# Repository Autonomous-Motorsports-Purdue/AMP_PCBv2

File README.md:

# AMP PCB version 2

This PCB attempts to refine the v1 PCB to strip away extraneous components and achieve the best minimal set of components needed for drive, steering, and braking control

## Features

| Name                    | Current Status         | Notes |
|-------------------------|------------------------|-------|
| Foot switch             | Working                | Master enable for motor controller
| Forward throttle        | Working                | -
| Reverse throttle        | Working                | -
| Motor brake control     | Untested               | Primary braking system if working
| Emergency brake control | Working                | Mechanical brake actuator
| Steering                | Working                | 0-100% PWM duty cycle control
| LoRa remote control     | Partially tested       | -
| Watchdog timer          | Broken on Rev A        | -
| Hardware serial port    | Working                | -

---

## Technical Information
- [Teensy 4.0 front pinout](docs/img/Teensy_40_Front_Pinout.png)
- [Teensy 4.0 rear pinout](docs/img/Teensy_40_Rear_Pinout.png)
- [Emergency brake controller truth table](docs/img/Brake_Control_Signals.png)

### Useful links
- [RC Low-pass Filter Design for PWM](http://sim.okawa-denshi.jp/en/PWMtool.php)
- [Software setup for Teensy with Arduino](https://www.pjrc.com/teensy/tutorial.html)

---

## Part Numbers
| Part Number | Description |
|-------------|-------------|
| [776164-1](https://www.digikey.com/en/products/detail/te-connectivity-deutsch-ict-connectors/776164-1/2183727) | AMPSEAL (main motor controller connector) 35-pin connector
| [770520-1](https://www.digikey.com/en/products/detail/te-connectivity-amp-connectors/770520-1/744981) | AMPSEAL crimps

---

## Miscellaneous notes (to check)

- Create documentation for connectors (especially motor controller connector)
- Create complete BOM for PCB

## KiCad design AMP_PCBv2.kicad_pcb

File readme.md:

# AMP PCB version 2

This PCB attempts to refine the v1 PCB to strip away extraneous components and achieve the best minimal set of components needed for drive, steering, and braking control

## Minimal Feature Set

- 0-12 volt analog throttle signal
- digital drive mode control (12 volt logic level)
  - Foot switch (FS1)
  - Forward (FWD)
  - Reverse (REV)
- 12 volt frequency modulated PWM steering signal
  - //TODO: ADD THE FREQUENCY BOUNDS OF FULL LEFT AND FULL RIGHT
- digital brake control (5 volt logic level //FIXME: IS THIS CORRECT?, CHECK IF THIS IS LEVEL SHIFTED ON CURRENT BOARD)
  - 

## Extensions

- E-Brake
- Remote control

## Notes (to check)

- Throttle differential amplifier
  - Check if gain can be larger/smaller than 3.63 (for resistor selection)
  - Low pass filter for PWM->analog signal
- Motor controller
  - Add breakout pins when PCB ordered/tested
- FTDI breakout (check if needed for Teensy)
- Feather
  - Remote control pins
- Connectors
  - Test point connectors
  - Signal out connectors (talk to electrical)

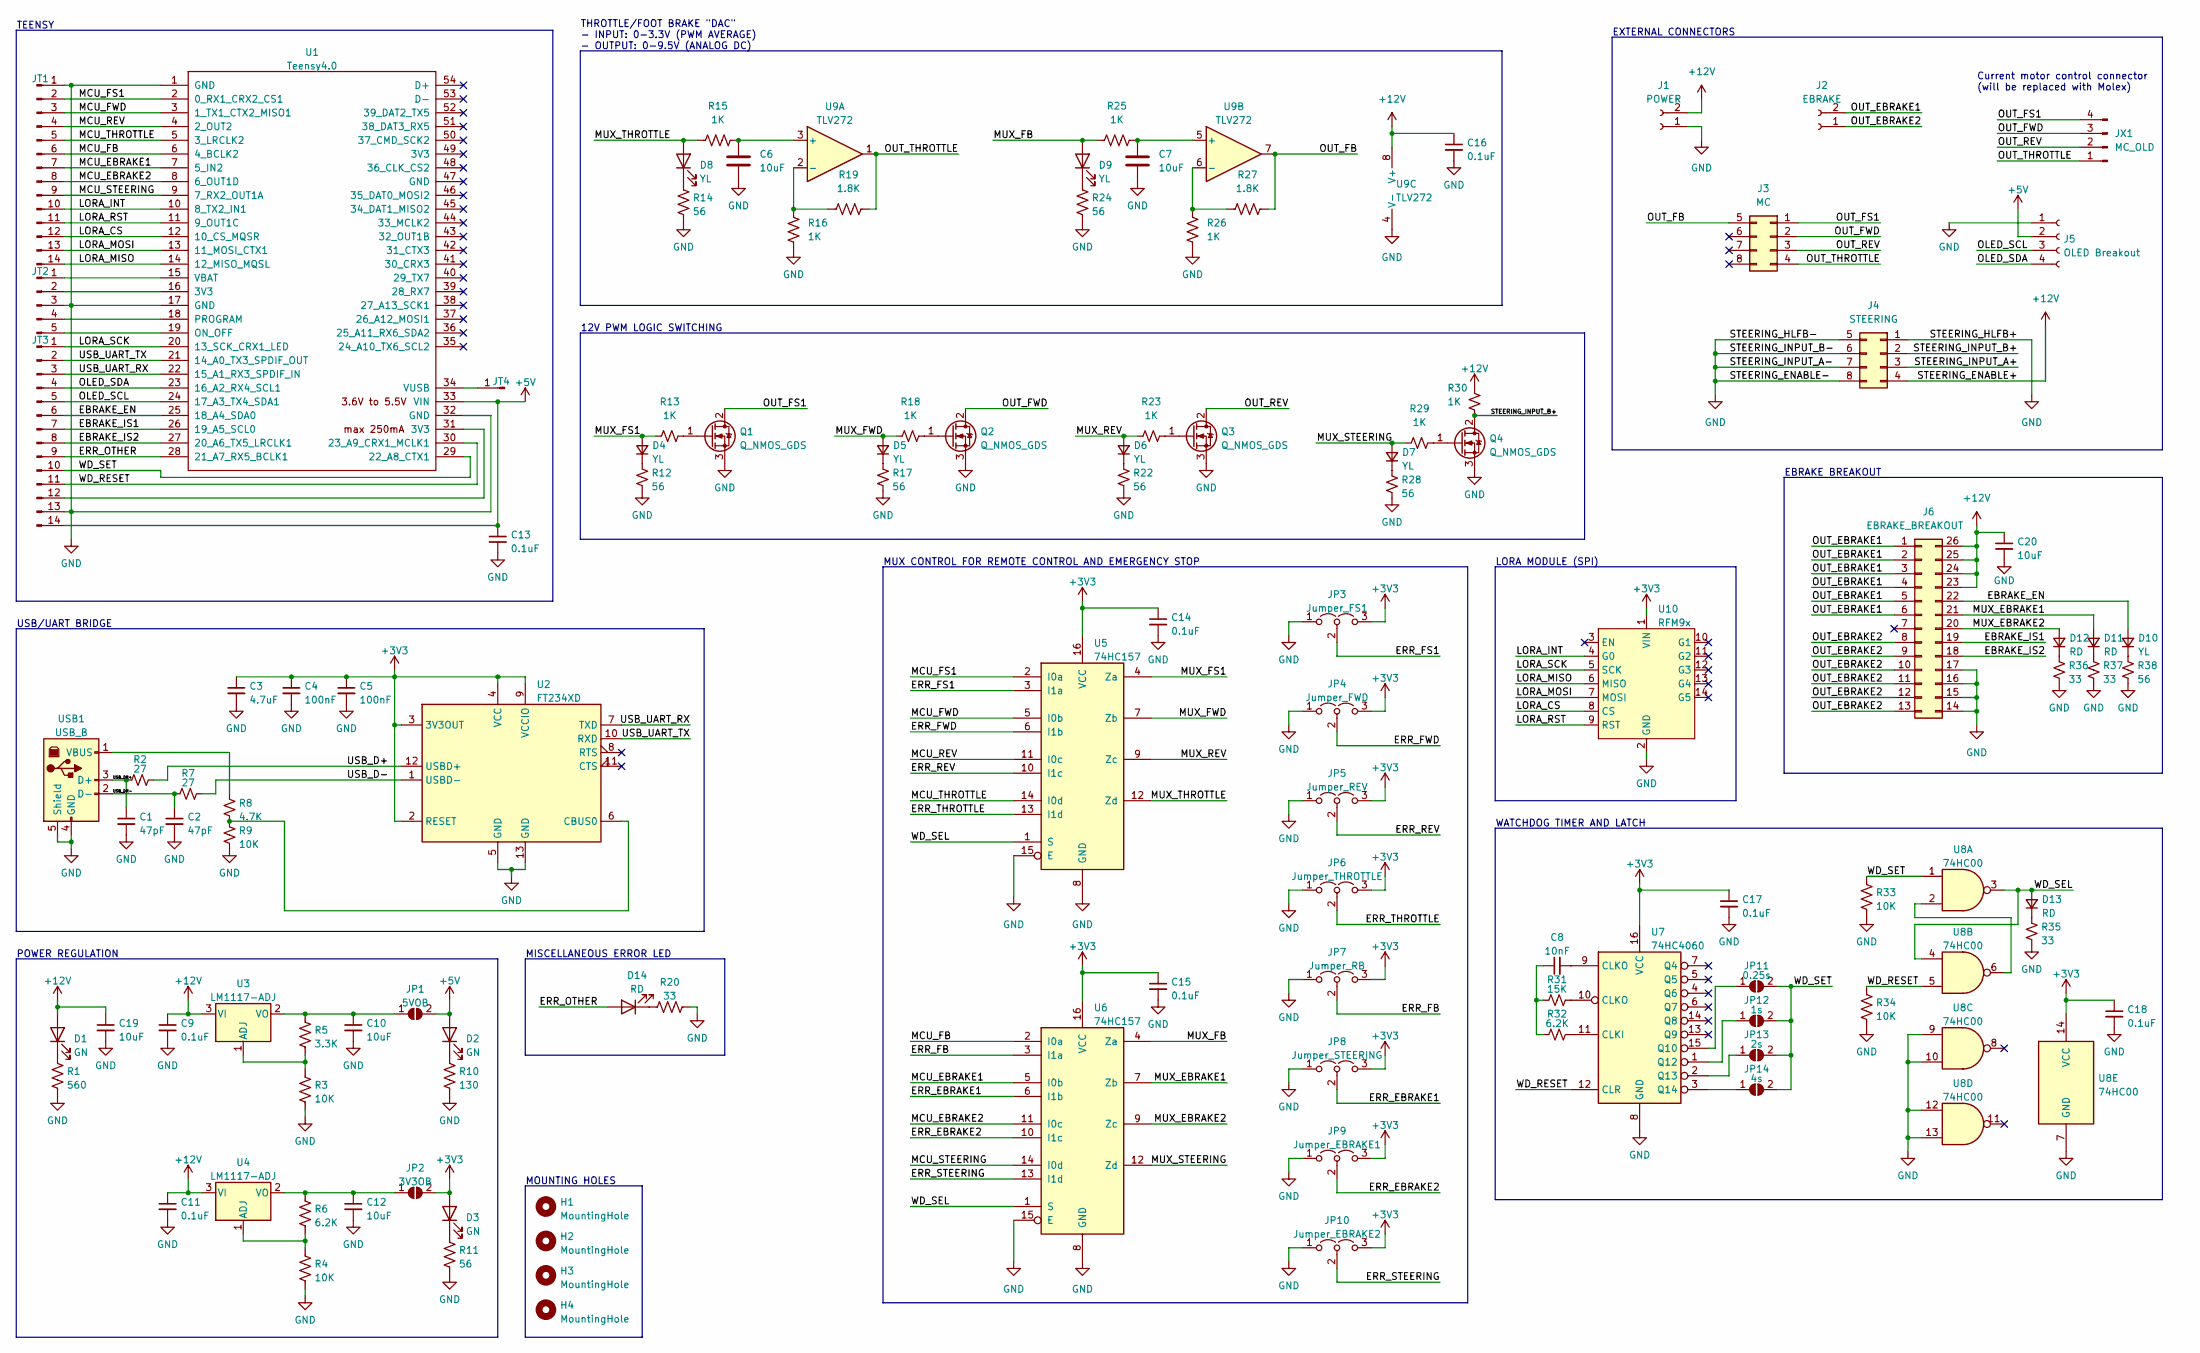
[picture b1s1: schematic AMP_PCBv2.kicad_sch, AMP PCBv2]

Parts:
C1, C2: 47pF; C_0805_2012Metric_Pad1.18x1.45mm_HandSolder
C3: 4.7uF; C_0805_2012Metric_Pad1.18x1.45mm_HandSolder
C4, C5: 100nF; C_0805_2012Metric_Pad1.18x1.45mm_HandSolder
C6, C7, C10, C12, C19, C20: 10uF; C_0805_2012Metric_Pad1.18x1.45mm_HandSolder
C8: 10nF; C_0805_2012Metric_Pad1.18x1.45mm_HandSolder
C9, C11, C13, C14, C15, C16, C17, C18: 0.1uF; C_0805_2012Metric_Pad1.18x1.45mm_HandSolder
D1, D2, D3: GN; LED_D5.0mm
D4, D5, D6, D7, D8, D9, D10: YL; LED_D5.0mm
D11, D12, D13, D14: RD; LED_D5.0mm
H1, H2, H3, H4: MountingHole; MountingHole_3.2mm_M3
J1: POWER; Molex_Mini-Fit_Jr_5566-02A_2x01_P4.20mm_Vertical
J2: EBRAKE; Molex_Mini-Fit_Jr_5566-02A_2x01_P4.20mm_Vertical
J3: MC; Molex_Mini-Fit_Jr_5566-08A_2x04_P4.20mm_Vertical
J4: STEERING; Molex_Mini-Fit_Jr_5566-08A_2x04_P4.20mm_Vertical
J5: OLED Breakout; PinSocket_1x04_P2.54mm_Vertical
J6: EBRAKE_BREAKOUT; AMP_Brake_Controller_Breakout
JP1: 5VOB; SolderJumper-2_P1.3mm_Open_TrianglePad1.0x1.5mm
JP2: 3V3OB; SolderJumper-2_P1.3mm_Open_TrianglePad1.0x1.5mm
JP3: Jumper_FS1; PinHeader_1x03_P2.54mm_Vertical
JP4: Jumper_FWD; PinHeader_1x03_P2.54mm_Vertical
JP5: Jumper_REV; PinHeader_1x03_P2.54mm_Vertical
JP6: Jumper_THROTTLE; PinHeader_1x03_P2.54mm_Vertical
JP7: Jumper_RB; PinHeader_1x03_P2.54mm_Vertical
JP8: Jumper_STEERING; PinHeader_1x03_P2.54mm_Vertical
JP9: Jumper_EBRAKE1; PinHeader_1x03_P2.54mm_Vertical
JP10: Jumper_EBRAKE2; PinHeader_1x03_P2.54mm_Vertical
JP11: 0.25s; SolderJumper-2_P1.3mm_Open_TrianglePad1.0x1.5mm
JP12: 1s; SolderJumper-2_P1.3mm_Open_TrianglePad1.0x1.5mm
JP13: 2s; SolderJumper-2_P1.3mm_Open_TrianglePad1.0x1.5mm
JP14: 4s; SolderJumper-2_P1.3mm_Open_TrianglePad1.0x1.5mm
JT1, JT3: Conn_01x14_Male; PinHeader_1x14_P2.54mm_Vertical
JT2: Conn_01x05_Male; PinHeader_1x05_P2.54mm_Vertical
JT4: Conn_01x01_Male; PinHeader_1x01_P2.54mm_Vertical
JX1: MC_OLD; Molex_KK-254_AE-6410-04A_1x04_P2.54mm_Vertical
Q1, Q2, Q3, Q4: Q_NMOS_GDS; TO-251-3_Vertical
R1: 560; R_0805_2012Metric_Pad1.20x1.40mm_HandSolder
R2, R7: 27; R_0805_2012Metric_Pad1.20x1.40mm_HandSolder
R3, R4, R9, R33, R34: 10K; R_0805_2012Metric_Pad1.20x1.40mm_HandSolder
R5: 3.3K; R_0805_2012Metric_Pad1.20x1.40mm_HandSolder
R6, R32: 6.2K; R_0805_2012Metric_Pad1.20x1.40mm_HandSolder
R8: 4.7K; R_0805_2012Metric_Pad1.20x1.40mm_HandSolder
R10: 130; R_0805_2012Metric_Pad1.20x1.40mm_HandSolder
R11, R12, R14, R17, R22, R24, R28, R38: 56; R_0805_2012Metric_Pad1.20x1.40mm_HandSolder
R13, R15, R16, R18, R23, R25, R26, R29, R30: 1K; R_0805_2012Metric_Pad1.20x1.40mm_HandSolder
R19, R27: 1.8K; R_0805_2012Metric_Pad1.20x1.40mm_HandSolder
R20, R35, R36, R37: 33; R_0805_2012Metric_Pad1.20x1.40mm_HandSolder
R31: 15K; R_0805_2012Metric_Pad1.20x1.40mm_HandSolder
U1: Teensy4.0; Teensy40
U2: FT234XD; DFN-12-1EP_3x3mm_P0.5mm_EP1.6x2.5mm
U3, U4: LM1117-ADJ; TO-220-3_Vertical
U5, U6: 74HC157; DIP-16_W7.62mm
U7: 74HC4060; DIP-16_W7.62mm
U8: 74HC00; DIP-14_W7.62mm
U9: TLV272; DIP-8_W7.62mm
U10: RFM9x; RFM9x_Adafruit
USB1: USB_B; USB_B_TE_5787834_Vertical

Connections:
+3V3: C3.1, C4.1, C5.1, C14.1, C15.1, C17.1, C18.1, D3.2 (A), JP2.2 (B), JP3.3 (B), JP4.3 (B), JP5.3 (B), JP6.3 (B), JP7.3 (B), JP8.3 (B), JP9.3 (B), JP10.3 (B), U2.2 (RESET), U2.3 (3V3OUT), U2.4 (VCC), U2.9 (VCCIO), U5.16 (VCC), U6.16 (VCC), U7.16 (VCC), U8.14 (VCC), U10.1 (VIN)
+5V: C13.1, D2.2 (A), J5.2, JP1.2 (B), JT3.14, U1.33 (VIN)
+12V: C9.1, C11.1, C16.1, C19.1, C20.1, D1.2 (A), J1.2, J4.4, J6.23, J6.24, J6.25, J6.26, R30.2, U3.3 (VI), U4.3 (VI), U9.8 (V+)
/EBRAKE_EN: D10.2 (A), J6.22, JT3.6, U1.25 (18_A4_SDA0)
/EBRAKE_IS1: J6.19, JT3.7, U1.26 (19_A5_SCL0)
/EBRAKE_IS2: J6.18, JT3.8, U1.27 (20_A6_TX5_LRCLK1)
/ERR_EBRAKE1: JP8.2 (C), U6.6 (I1b)
/ERR_EBRAKE2: JP9.2 (C), U6.10 (I1c)
/ERR_FB: JP7.2 (C), U6.3 (I1a)
/ERR_FS1: JP3.2 (C), U5.3 (I1a)
/ERR_FWD: JP4.2 (C), U5.6 (I1b)
/ERR_OTHER: D14.2 (A), JT3.9, U1.28 (21_A7_RX5_BCLK1)
/ERR_REV: JP5.2 (C), U5.10 (I1c)
/ERR_STEERING: JP10.2 (C), U6.13 (I1d)
/ERR_THROTTLE: JP6.2 (C), U5.13 (I1d)
/LORA_CS: JT1.12, U1.12 (10_CS_MQSR), U10.8 (CS)
/LORA_INT: JT1.10, U1.10 (8_TX2_IN1), U10.4 (G0)
/LORA_MISO: JT1.14, U1.14 (12_MISO_MQSL), U10.6 (MISO)
/LORA_MOSI: JT1.13, U1.13 (11_MOSI_CTX1), U10.7 (MOSI)
/LORA_RST: JT1.11, U1.11 (9_OUT1C), U10.9 (RST)
/LORA_SCK: JT3.1, U1.20 (13_SCK_CRX1_LED), U10.5 (SCK)
/MCU_EBRAKE1: JT1.7, U1.7 (5_IN2), U6.5 (I0b)
/MCU_EBRAKE2: JT1.8, U1.8 (6_OUT1D), U6.11 (I0c)
/MCU_FB: JT1.6, U1.6 (4_BCLK2), U6.2 (I0a)
/MCU_FS1: JT1.2, U1.2 (0_RX1_CRX2_CS1), U5.2 (I0a)
/MCU_FWD: JT1.3, U1.3 (1_TX1_CTX2_MISO1), U5.5 (I0b)
/MCU_REV: JT1.4, U1.4 (2_OUT2), U5.11 (I0c)
/MCU_STEERING: JT1.9, U1.9 (7_RX2_OUT1A), U6.14 (I0d)
/MCU_THROTTLE: JT1.5, U1.5 (3_LRCLK2), U5.14 (I0d)
/MUX_EBRAKE1: D11.2 (A), J6.21, U6.7 (Zb)
/MUX_EBRAKE2: D12.2 (A), J6.20, U6.9 (Zc)
/MUX_FB: D9.2 (A), R25.1, U6.4 (Za)
/MUX_FS1: D4.2 (A), R13.1, U5.4 (Za)
/MUX_FWD: D5.2 (A), R18.1, U5.7 (Zb)
/MUX_REV: D6.2 (A), R23.1, U5.9 (Zc)
/MUX_STEERING: D7.2 (A), R29.1, U6.12 (Zd)
/MUX_THROTTLE: D8.2 (A), R15.1, U5.12 (Zd)
/OLED_SCL: J5.3, JT3.5, U1.24 (17_A3_TX4_SDA1)
/OLED_SDA: J5.4, JT3.4, U1.23 (16_A2_RX4_SCL1)
/OUT_EBRAKE1: J2.2, J6.1, J6.2, J6.3, J6.4, J6.5, J6.6
/OUT_EBRAKE2: J2.1, J6.8, J6.9, J6.10, J6.11, J6.12, J6.13
/OUT_FB: J3.5, R27.2, U9.7
/OUT_FS1: J3.1, JX1.4, Q1.2 (D)
/OUT_FWD: J3.2, JX1.3, Q2.2 (D)
/OUT_REV: J3.3, JX1.2, Q3.2 (D)
/OUT_THROTTLE: J3.4, JX1.1, R19.2, U9.1
/STEERING_INPUT_A+: J4.3
/STEERING_INPUT_B+: J4.2, Q4.2 (D), R30.1
/USB_D+: R2.2, U2.12 (USBD+)
/USB_D-: R7.2, U2.1 (USBD-)
/USB_DR+: C1.1, R2.1, USB1.3 (D+)
/USB_DR-: C2.1, R7.1, USB1.2 (D-)
/USB_UART_RX: JT3.3, U1.22 (15_A1_RX3_SPDIF_IN), U2.7 (TXD)
/USB_UART_TX: JT3.2, U1.21 (14_A0_TX3_SPDIF_OUT), U2.10 (RXD)
/WD_RESET: JT3.11, R34.1, U1.30 (23_A9_CRX1_MCLK1), U7.12 (CLR), U8.5
/WD_SEL: D13.2 (A), U5.1 (S), U6.1 (S), U8.3, U8.4
/WD_SET: JP11.2 (B), JP12.2 (B), JP13.2 (B), JP14.2 (B), JT3.10, R33.1, U1.29 (22_A8_CTX1), U8.1
GND: C1.2, C2.2, C3.2, C4.2, C5.2, C6.2, C7.2, C9.2, C10.2, C11.2, C12.2, C13.2, C14.2, C15.2, C16.2, C17.2, C18.2, C19.2, C20.2, J1.1, J4.1, J4.5, J4.6, J4.7, J4.8, J5.1, J6.14, J6.15, J6.16, J6.17, JP3.1 (A), JP4.1 (A), JP5.1 (A), JP6.1 (A), JP7.1 (A), JP8.1 (A), JP9.1 (A), JP10.1 (A), JT1.1, JT2.3, JT3.13, Q1.3 (S), Q2.3 (S), Q3.3 (S), Q4.3 (S), R1.2, R3.1, R4.1, R9.2, R10.2, R11.2, R12.2, R14.2, R16.2, R17.2, R20.2, R22.2, R24.2, R26.2, R28.2, R33.2, R34.2, R35.2, R36.2, R37.2, R38.2, U1.1 (GND), U1.17 (GND), U1.32 (GND), U2.5 (GND), U2.13 (GND), U5.8 (GND), U5.15 (E), U6.8 (GND), U6.15 (E), U7.8 (GND), U8.7 (GND), U8.9, U8.10, U8.12, U8.13, U9.4 (V-), U10.2 (GND), USB1.4 (GND), USB1.5 (Shield)
unnamed: C6.1, R15.2, U9.3 (+)
unnamed: C7.1, R25.2, U9.5 (+)
unnamed: C8.1, R31.1, R32.1
unnamed: C8.2, U7.9 (CLKO)
unnamed: C10.1, JP1.1 (A), R5.1, U3.2 (VO)
unnamed: C12.1, JP2.1 (A), R6.1, U4.2 (VO)
unnamed: D1.1 (K), R1.1
unnamed: D2.1 (K), R10.1
unnamed: D3.1 (K), R11.1
unnamed: D4.1 (K), R12.1
unnamed: D5.1 (K), R17.1
unnamed: D6.1 (K), R22.1
unnamed: D7.1 (K), R28.1
unnamed: D8.1 (K), R14.1
unnamed: D9.1 (K), R24.1
unnamed: D10.1 (K), R38.1
unnamed: D11.1 (K), R37.1
unnamed: D12.1 (K), R36.1
unnamed: D13.1 (K), R35.1
unnamed: D14.1 (K), R20.1
unnamed: JP11.1 (A), U7.15 (Q10)
unnamed: JP12.1 (A), U7.1 (Q12)
unnamed: JP13.1 (A), U7.2 (Q13)
unnamed: JP14.1 (A), U7.3 (Q14)
unnamed: JT2.1, U1.15 (VBAT)
unnamed: JT2.2, U1.16 (3V3)
unnamed: JT2.4, U1.18 (PROGRAM)
unnamed: JT2.5, U1.19 (ON_OFF)
unnamed: JT3.12, U1.31 (3V3)
unnamed: JT4.1, U1.34 (VUSB)
unnamed: Q1.1 (G), R13.2
unnamed: Q2.1 (G), R18.2
unnamed: Q3.1 (G), R23.2
unnamed: Q4.1 (G), R29.2
unnamed: R3.2, R5.2, U3.1 (ADJ)
unnamed: R4.2, R6.2, U4.1 (ADJ)
unnamed: R8.1, USB1.1 (VBUS)
unnamed: R8.2, R9.1, U2.6 (CBUS0)
unnamed: R16.1, R19.1, U9.2 (-)
unnamed: R26.1, R27.1, U9.6 (-)
unnamed: R31.2, U7.10 (CLKO)
unnamed: R32.2, U7.11 (CLKI)
unnamed: U8.2, U8.6

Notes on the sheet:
EBRAKE BREAKOUT
MISCELLANEOUS ERROR LED
WATCHDOG TIMER AND LATCH
MOUNTING HOLES
POWER REGULATION
EXTERNAL CONNECTORS
THROTTLE/FOOT BRAKE "DAC" - INPUT: 0-3.3V (PWM AVERAGE) - OUTPUT: 0-9.5V (ANALOG DC)
12V PWM LOGIC SWITCHING
TEENSY
LORA MODULE (SPI)
USB/UART BRIDGE
Current motor control connector (will be replaced with Molex)
MUX CONTROL FOR REMOTE CONTROL AND EMERGENCY STOP

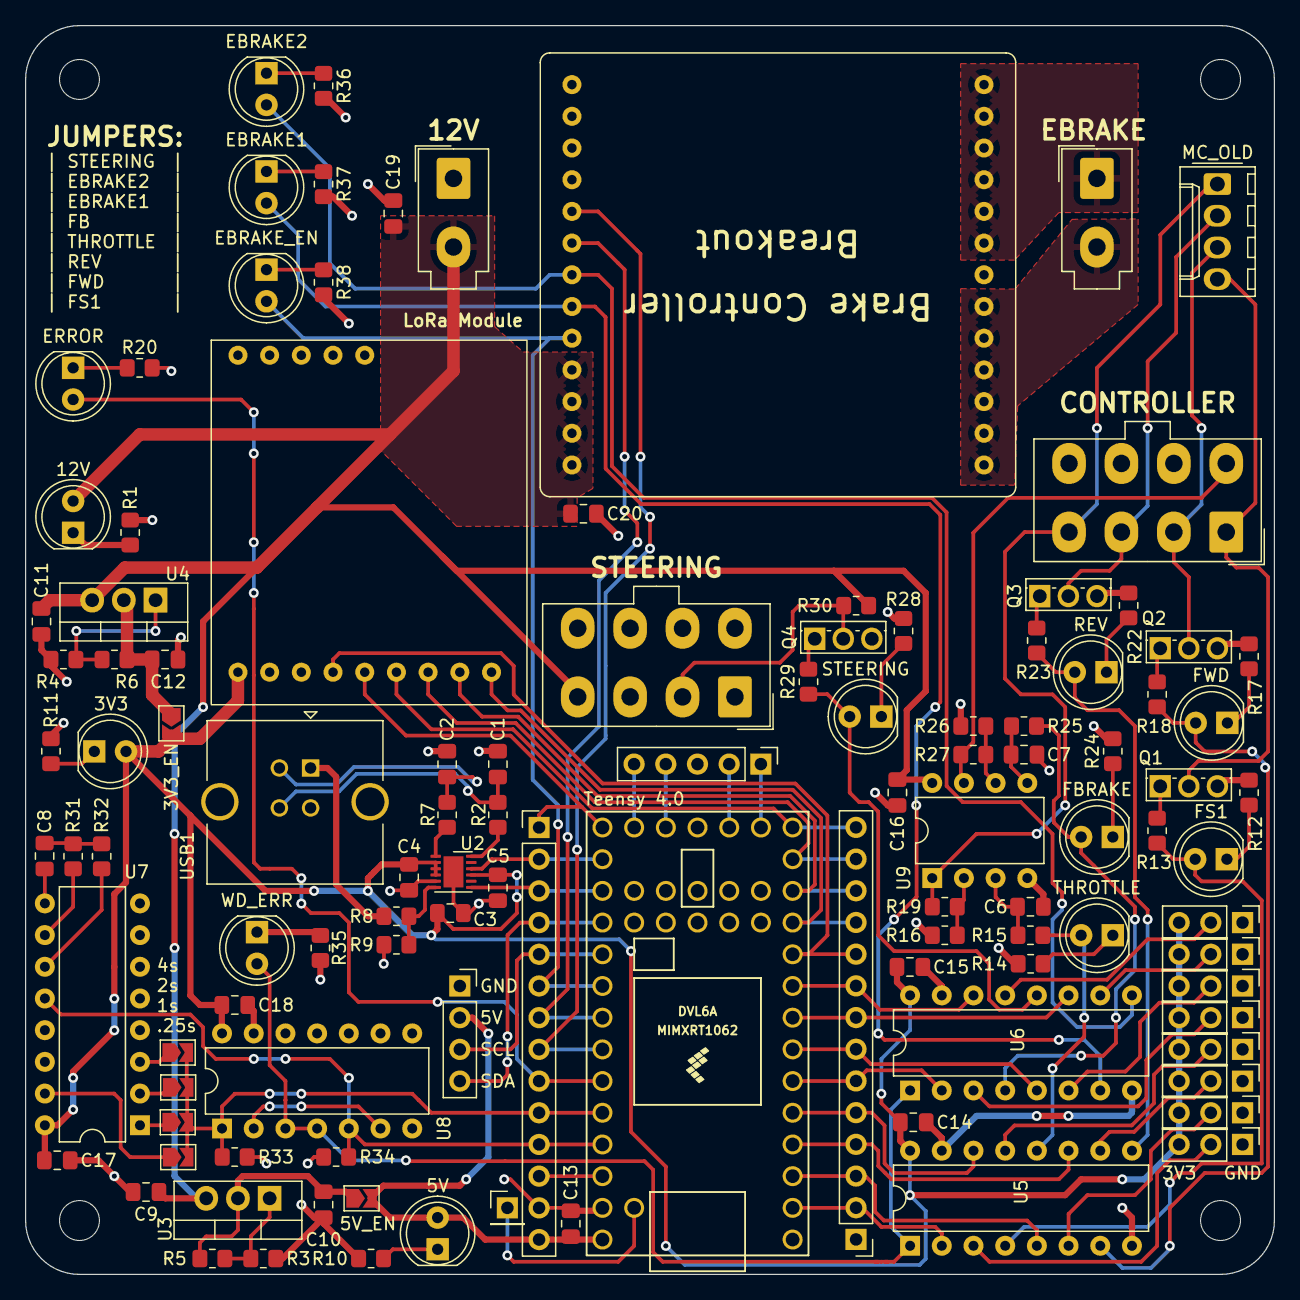
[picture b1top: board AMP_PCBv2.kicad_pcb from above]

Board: 2 copper layers, 100.1 x 100.1 mm, 115 parts (0 on the bottom side), 100 nets.

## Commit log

2022-03-31 Add to-do list notes
2022-03-31 added bare bones schematic
2022-04-06 Add MOSFET gate resistors, other misc cleanup
2022-04-06 Add datasheets
2022-04-07 Add documentation
2022-04-21 added breadboard testing folder
2022-10-23 Update steering MOSFET configuration
2022-10-31 Add mux chain, foot brake amplifier; schematic cleanup
2022-11-05 Add wire-board connectors
2022-11-05 Update op-amp PN and add e-brake breakout
2022-11-05 Remove logo schematic designator
2022-11-06 Add AMPSEAL crimp part number
2022-11-06 Add AMPSEAL connector part number
2022-12-09 Change DAC op-amp gain
2022-12-23 Add 74HC4060 library
2022-12-23 Add FT234XD library
2022-12-23 Add custom libraries to project
2022-12-23 Add watchdog timer, USB/UART, power regulators, finish pin connections and add annotations
2022-12-23 Add brake controller breakout footprint
2022-12-23 Add decoupling capacitors and assign footprints
2022-12-23 Change OLED screen footprint
2022-12-23 Route PCB
2022-12-23 Add logo and label text
2022-12-24 Route differential pair for USB connection
2022-12-26 Add LoRa module and extra decoupling capacitors
2022-12-26 Route new PCB (with LoRa)
2022-12-26 Add 3D models
2022-12-26 Update library structure
2022-12-26 Add extra error LED
2022-12-26 Schematic clean up
2022-12-27 Fix #3
2022-12-27 Generate gerber files for Revision A
2023-01-10 Add ibom
2023-01-10 Update datasheets
2023-01-10 Add Teensy pinout images
2023-01-10 Update README with more information
2023-01-12 Fix D+/D- flipped #4
2023-01-12 Increase thickness of some traces to 0.3mm
2023-01-12 Classify project as Revision B
2023-01-12 Add PCB drawing files
2023-01-12 Move ibom location
2023-01-14 Add OLED connector labels #9
2023-01-14 Fix jumper label text #6
2023-01-14 Change PCB info text to be relative to KiCad file
2023-01-16 Update README after testing
2023-01-16 Change 'Completed' to 'Working'
